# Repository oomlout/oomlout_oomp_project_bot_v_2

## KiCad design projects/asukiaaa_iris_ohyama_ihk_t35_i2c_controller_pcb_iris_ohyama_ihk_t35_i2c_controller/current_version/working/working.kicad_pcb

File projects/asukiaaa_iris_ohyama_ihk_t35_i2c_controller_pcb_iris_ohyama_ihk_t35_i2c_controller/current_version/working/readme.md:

# iris_ohyama_ihk_t35_i2c_controller_pcb
 
## summary 
* id: asukiaaa_iris_ohyama_ihk_t35_i2c_controller_pcb_iris_ohyama_ihk_t35_i2c_controller
* user: asukiaaa
* name: iris_ohyama_ihk_t35_i2c_controller_pcb
* board: iris_ohyama_ihk_t35_i2c_controller
* repo: https://github.com/asukiaaa/IRIS-OHYAMA-IHK-T35-I2C-Controller-PCB
* src_file_repo_kicad_pcb: main_pcb/IRIS-OHYAMA-IHK-T35-I2C-Controller.kicad_pcb
* src_file_repo_kicad_pcb_link: https://github.com/asukiaaa/IRIS-OHYAMA-IHK-T35-I2C-Controller-PCB/tree/master/main_pcb/IRIS-OHYAMA-IHK-T35-I2C-Controller.kicad_pcb

* src_file_repo_sch: main_pcb/IRIS-OHYAMA-IHK-T35-I2C-Controller.sch
* src_file_repo_sch_link: https://github.com/asukiaaa/IRIS-OHYAMA-IHK-T35-I2C-Controller-PCB/tree/master/main_pcb/IRIS-OHYAMA-IHK-T35-I2C-Controller.sch
* full details link: https://github.com/oomlout/oomlout_oomp_project_bot_v_2/tree/main/projects/asukiaaa_iris_ohyama_ihk_t35_i2c_controller_pcb_iris_ohyama_ihk_t35_i2c_controller/current_version/working  

## schematic  
  
[schematic (pdf)](working_schematic.pdf) 

## pcb  

[board (pdf)](working.pdf)  

## working_bom
| Id | Designator | Footprint | Quantity | Designation | Supplier and ref |  | None | 
| --- | --- | --- | --- | --- | --- | --- | --- | 
| 1 | J3 | JST_XH_S2B-XH-A_1x02_P2.50mm_Horizontal | 1 | thermistor |  |  | [''] | 
| 2 | C1,C2 | C_0402_1005Metric | 2 | 0.1uf |  |  | [''] | 
| 3 | CN1 | JST_XH_S5B-XH-A_1x05_P2.50mm_Horizontal | 1 | Conn_01x05 |  |  | [''] | 
| 4 | D1 | LED_0603_1608Metric | 1 | Level1 |  |  | [''] | 
| 5 | D2 | LED_0603_1608Metric | 1 | Level2 |  |  | [''] | 
| 6 | D3 | LED_0603_1608Metric | 1 | Level3 |  |  | [''] | 
| 7 | D4 | LED_0603_1608Metric | 1 | Level4 |  |  | [''] | 
| 8 | D5 | LED_0603_1608Metric | 1 | Level5 |  |  | [''] | 
| 9 | D6 | LED_0603_1608Metric | 1 | Level6 |  |  | [''] | 
| 10 | D7 | LED_0603_1608Metric | 1 | NomalState |  |  | [''] | 
| 11 | D8 | LED_0603_1608Metric | 1 | OilState |  |  | [''] | 
| 12 | D9,D10,D11,D12,D13,D14 | D_SOD-123F | 6 | D |  |  | [''] | 
| 13 | J1 | NS-Tech_Grove_1x04_P2mm_Horizontal | 1 | Grove |  |  | [''] | 
| 14 | KEY1 | SW_PUSH_6mm_center_like_smd | 1 | normal_power |  |  | [''] | 
| 15 | KEY2 | SW_PUSH_6mm_center_like_smd | 1 | power_up |  |  | [''] | 
| 16 | KEY3 | SW_PUSH_6mm_center_like_smd | 1 | power_down |  |  | [''] | 
| 17 | KEY5 | SW_PUSH_6mm_center_like_smd | 1 | oil_power |  |  | [''] | 
| 18 | Q1,Q2,Q3,Q4 | SOT-23 | 4 | Q_NMOS_DGS |  |  | [''] | 
| 19 | R1,R2,R3,R4,R5,R6,R7,R8,R12,R14,R15,R16,R17,R18,R19,R20 | R_0603_1608Metric | 16 | 1k |  |  | [''] | 
| 20 | R9,R10,R11,R13 | R_0603_1608Metric | 4 | 2k |  |  | [''] | 
| 21 | U1 | SOP-14_4.4x9.2mm_P1.27mm | 1 | 74HC164 |  |  | [''] | 
| 22 | U2 | QFN-32-1EP_5x5mm_P0.5mm_EP3.1x3.1mm | 1 | ATmega328P-MU |  |  | [''] | 
| 23 | J2 | 2x03_P2.54mm_Pads | 1 | Conn_01x06 |  |  | [''] | 

## bom_schematic
| Ref | Qnty | Value | Cmp name | Footprint | Description | Vendor | DNP | 
| --- | --- | --- | --- | --- | --- | --- | --- | 
| C1, C2 | 2 | 0.1uf | C | Capacitor_SMD:C_0402_1005Metric | Unpolarized capacitor |  |  | 
| CN1 | 1 | Conn_01x05 | Conn_01x05 | Connector_JST:JST_XH_S5B-XH-A_1x05_P2.50mm_Horizontal | Generic connector, single row, 01x05, script generated (kicad-library-utils/schlib/autogen/connector/) |  |  | 
| D1 | 1 | Level1 | LED | LED_SMD:LED_0603_1608Metric | Light emitting diode |  |  | 
| D2 | 1 | Level2 | LED | LED_SMD:LED_0603_1608Metric | Light emitting diode |  |  | 
| D3 | 1 | Level3 | LED | LED_SMD:LED_0603_1608Metric | Light emitting diode |  |  | 
| D4 | 1 | Level4 | LED | LED_SMD:LED_0603_1608Metric | Light emitting diode |  |  | 
| D5 | 1 | Level5 | LED | LED_SMD:LED_0603_1608Metric | Light emitting diode |  |  | 
| D6 | 1 | Level6 | LED | LED_SMD:LED_0603_1608Metric | Light emitting diode |  |  | 
| D7 | 1 | NomalState | LED | LED_SMD:LED_0603_1608Metric | Light emitting diode |  |  | 
| D8 | 1 | OilState | LED | LED_SMD:LED_0603_1608Metric | Light emitting diode |  |  | 
| D9, D10, D11, D12, D13, D14 | 6 | D | D | Diode_SMD:D_SOD-123F | Diode |  |  | 
| J1 | 1 | Grove | Conn_01x04 | my-kicad-footprints:NS-Tech_Grove_1x04_P2mm_Horizontal | Generic connector, single row, 01x04, script generated (kicad-library-utils/schlib/autogen/connector/) |  |  | 
| J2 | 1 | Conn_01x06 | Conn_01x06 | my-kicad-footprints:2x03_P2.54mm_Pads | Generic connector, single row, 01x06, script generated (kicad-library-utils/schlib/autogen/connector/) |  |  | 
| J3 | 1 | thermistor | Conn_01x02 | Connector_JST:JST_XH_S2B-XH-A_1x02_P2.50mm_Horizontal | Generic connector, single row, 01x02, script generated (kicad-library-utils/schlib/autogen/connector/) |  |  | 
| JP1 | 1 | ADDR0_NO | Jumper_NO_Small-Device | Jumper:SolderJumper-2_P1.3mm_Open_RoundedPad1.0x1.5mm |  |  |  | 
| JP2 | 1 | ADDR1_NO | Jumper_NO_Small-Device | Jumper:SolderJumper-2_P1.3mm_Open_RoundedPad1.0x1.5mm |  |  |  | 
| KEY1 | 1 | normal_power | SW_Push | footprints:SW_PUSH_6mm_center_like_smd | Push button switch, generic, two pins |  |  | 
| KEY2 | 1 | power_up | SW_Push | footprints:SW_PUSH_6mm_center_like_smd | Push button switch, generic, two pins |  |  | 
| KEY3 | 1 | power_down | SW_Push | footprints:SW_PUSH_6mm_center_like_smd | Push button switch, generic, two pins |  |  | 
| KEY5 | 1 | oil_power | SW_Push | footprints:SW_PUSH_6mm_center_like_smd | Push button switch, generic, two pins |  |  | 
| Q1, Q2, Q3, Q4 | 4 | Q_NMOS_GSD | Q_NMOS_GSD | Package_TO_SOT_SMD:SOT-23 | N-MOSFET transistor, gate/source/drain |  |  | 
| R1, R2, R3, R4, R5, R6, R7, R8, R12, R14, R15, R16, R17, R18, R19, R20 | 16 | 1k | R | Resistor_SMD:R_0603_1608Metric | Resistor |  |  | 
| R9, R10, R11, R13 | 4 | 2k | R | Resistor_SMD:R_0603_1608Metric | Resistor |  |  | 
| U1 | 1 | 74HC164 | 74HC164 | footprints:SOP-14_4.4x9.2mm_P1.27mm | 8-bit serial-in parallel-out shift register |  |  | 
| U2 | 1 | ATmega328P-MU | ATmega328PB-MU-MCU_Microchip_ATmega | Package_DFN_QFN:QFN-32-1EP_5x5mm_P0.5mm_EP3.1x3.1mm |  |  |  |

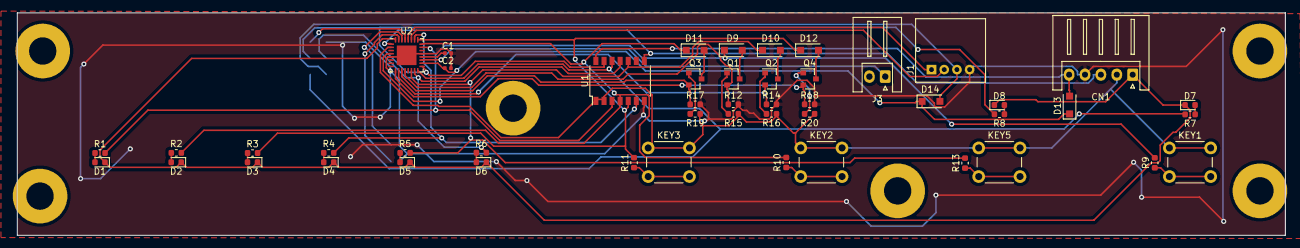
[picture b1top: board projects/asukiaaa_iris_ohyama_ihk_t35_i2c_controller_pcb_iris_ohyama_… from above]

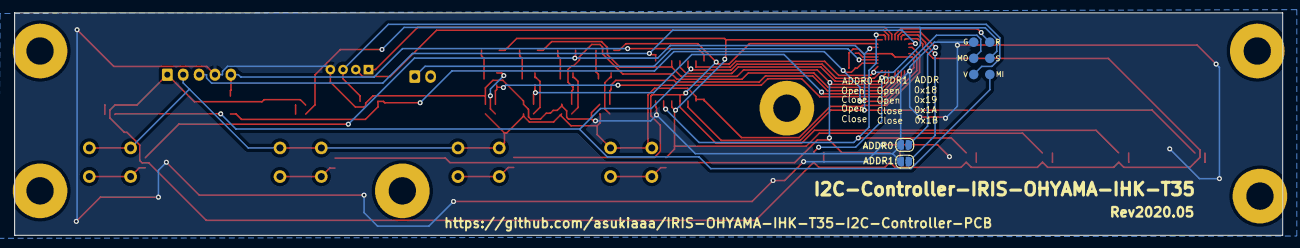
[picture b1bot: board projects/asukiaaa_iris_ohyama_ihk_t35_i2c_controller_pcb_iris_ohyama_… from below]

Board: 2 copper layers, 199.5 x 35.0 mm, 58 parts (3 on the bottom side), 46 nets.

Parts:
C1, C2: 0.1uf; C_0402_1005Metric
CN1: Conn_01x05; JST_XH_S5B-XH-A_1x05_P2.50mm_Horizontal
D1: Level1; LED_0603_1608Metric
D2: Level2; LED_0603_1608Metric
D3: Level3; LED_0603_1608Metric
D4: Level4; LED_0603_1608Metric
D5: Level5; LED_0603_1608Metric
D6: Level6; LED_0603_1608Metric
D7: NomalState; LED_0603_1608Metric
D8: OilState; LED_0603_1608Metric
D9, D10, D11, D12, D13, D14: D; D_SOD-123F
J1: Grove; NS-Tech_Grove_1x04_P2mm_Horizontal
J2: Conn_01x06; 2x03_P2.54mm_Pads
J3: thermistor; JST_XH_S2B-XH-A_1x02_P2.50mm_Horizontal
JP1: ADDR0_NO; SolderJumper-2_P1.3mm_Open_RoundedPad1.0x1.5mm
JP2: ADDR1_NO; SolderJumper-2_P1.3mm_Open_RoundedPad1.0x1.5mm
KEY1: normal_power; SW_PUSH_6mm_center_like_smd
KEY2: power_up; SW_PUSH_6mm_center_like_smd
KEY3: power_down; SW_PUSH_6mm_center_like_smd
KEY5: oil_power; SW_PUSH_6mm_center_like_smd
Q1, Q2, Q3, Q4: Q_NMOS_DGS; SOT-23
R1, R2, R3, R4, R5, R6, R7, R8, R12, R14, R15, R16, R17, R18, R19, R20: 1k; R_0603_1608Metric
R9, R10, R11, R13: 2k; R_0603_1608Metric
REF1, REF2, REF3, REF4, REF5, REF6: MountingHole_4.3mm_M4_Pad
U1: 74HC164; SOP-14_4.4x9.2mm_P1.27mm
U2: ATmega328P-MU; QFN-32-1EP_5x5mm_P0.5mm_EP3.1x3.1mm

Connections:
+5V: CN1.5, D13.2, U1.14
/A0: D9.1, R1.2, R9.2, U1.3, U2.23
/A1: D11.1, R2.2, R10.2, U1.4, U2.24
/A2: D12.1, R3.2, R11.2, U1.5, U2.25
/A3: R4.2, U1.6, U2.26
/A6: J3.1, U2.19
/ADDR0: JP1.1, U2.30
/ADDR1: JP2.1, U2.31
/CLK: CN1.3, U1.8, U2.1
/Controller_5V: C2.1, D13.1, D14.1, U2.4, U2.18
/D2: CN1.1, D1.1, D2.1, D3.1, D4.1, D5.1, D6.1, D7.1, D8.1, U2.32
/D4: CN1.2, KEY1.1, KEY2.1, KEY3.1, KEY5.1, R15.1, R16.1, R19.1, R20.1, U1.1, U1.2, U2.2
/D5: Q4.2, R18.1, U2.9
/D6: Q2.2, R14.1, U2.10
/D7: Q3.2, R17.1, U2.11
/D8: Q1.2, R12.1, U2.12
/D10: D10.1, R5.2, R13.2, U1.10, U2.14
/D11: J2.4, R6.2, U1.11, U2.15
/D12: J2.1, R7.2, U1.12, U2.16
/D13: J2.3, R8.2, U1.13, U2.17
/GROVE_5V: D14.2, J1.3, J2.2
/RST: J2.5, U2.29
/SCL: J1.1, U2.28
/SDA: J1.2, U2.27
GND: C1.2, C2.2, CN1.4, J1.4, J2.6, JP1.2, JP2.2, R12.2, R14.2, R17.2, R18.2, U1.7, U2.5, U2.21, U2.33
unnamed: C1.1, U2.20
unnamed: D1.2, R1.1
unnamed: D2.2, R2.1
unnamed: D3.2, R3.1
unnamed: D4.2, R4.1
unnamed: D5.2, R5.1
unnamed: D6.2, R6.1
unnamed: D7.2, R7.1
unnamed: D8.2, R8.1
unnamed: D9.2, Q1.3
unnamed: D10.2, Q2.3
unnamed: D11.2, Q3.3
unnamed: D12.2, Q4.3
unnamed: KEY1.2, R9.1
unnamed: KEY2.2, R10.1
unnamed: KEY3.2, R11.1
unnamed: KEY5.2, R13.1
unnamed: Q1.1, R15.2
unnamed: Q2.1, R16.2
unnamed: Q3.1, R19.2
unnamed: Q4.1, R20.2

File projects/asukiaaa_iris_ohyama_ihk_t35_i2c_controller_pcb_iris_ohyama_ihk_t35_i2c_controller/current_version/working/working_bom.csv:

"Id";"Designator";"Footprint";"Quantity";"Designation";"Supplier and ref";
1;"J3";"JST_XH_S2B-XH-A_1x02_P2.50mm_Horizontal";1;"thermistor";;;
2;"C1,C2";"C_0402_1005Metric";2;"0.1uf";;;
3;"CN1";"JST_XH_S5B-XH-A_1x05_P2.50mm_Horizontal";1;"Conn_01x05";;;
4;"D1";"LED_0603_1608Metric";1;"Level1";;;
5;"D2";"LED_0603_1608Metric";1;"Level2";;;
6;"D3";"LED_0603_1608Metric";1;"Level3";;;
7;"D4";"LED_0603_1608Metric";1;"Level4";;;
8;"D5";"LED_0603_1608Metric";1;"Level5";;;
9;"D6";"LED_0603_1608Metric";1;"Level6";;;
10;"D7";"LED_0603_1608Metric";1;"NomalState";;;
11;"D8";"LED_0603_1608Metric";1;"OilState";;;
12;"D9,D10,D11,D12,D13,D14";"D_SOD-123F";6;"D";;;
13;"J1";"NS-Tech_Grove_1x04_P2mm_Horizontal";1;"Grove";;;
14;"KEY1";"SW_PUSH_6mm_center_like_smd";1;"normal_power";;;
15;"KEY2";"SW_PUSH_6mm_center_like_smd";1;"power_up";;;
16;"KEY3";"SW_PUSH_6mm_center_like_smd";1;"power_down";;;
17;"KEY5";"SW_PUSH_6mm_center_like_smd";1;"oil_power";;;
18;"Q1,Q2,Q3,Q4";"SOT-23";4;"Q_NMOS_DGS";;;
19;"R1,R2,R3,R4,R5,R6,R7,R8,R12,R14,R15,R16,R17,R18,R19,R20";"R_0603_1608Metric";16;"1k";;;
20;"R9,R10,R11,R13";"R_0603_1608Metric";4;"2k";;;
21;"U1";"SOP-14_4.4x9.2mm_P1.27mm";1;"74HC164";;;
22;"U2";"QFN-32-1EP_5x5mm_P0.5mm_EP3.1x3.1mm";1;"ATmega328P-MU";;;
23;"J2";"2x03_P2.54mm_Pads";1;"Conn_01x06";;;

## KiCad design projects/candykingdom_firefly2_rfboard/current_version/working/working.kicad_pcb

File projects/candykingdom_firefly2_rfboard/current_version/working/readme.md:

# firefly2
 
## summary 
* id: candykingdom_firefly2_rfboard
* user: candykingdom
* name: firefly2
* board: rfboard
* repo: https://github.com/candykingdom/firefly2
* src_file_repo_kicad_pcb: hardware/rfboard/rfboard.kicad_pcb
* src_file_repo_kicad_pcb_link: https://github.com/candykingdom/firefly2/tree/master/hardware/rfboard/rfboard.kicad_pcb
* src_file_repo_kicad_sch: hardware/magnet-connector/magnet-connector.kicad_sch
* src_file_repo_kicad_sch_link: https://github.com/candykingdom/firefly2/tree/master/hardware/magnet-connector/magnet-connector.kicad_sch

* src_file_repo_sch: hardware/rfboard/rfboard.sch
* src_file_repo_sch_link: https://github.com/candykingdom/firefly2/tree/master/hardware/rfboard/rfboard.sch
* full details link: https://github.com/oomlout/oomlout_oomp_project_bot_v_2/tree/main/projects/candykingdom_firefly2_rfboard/current_version/working

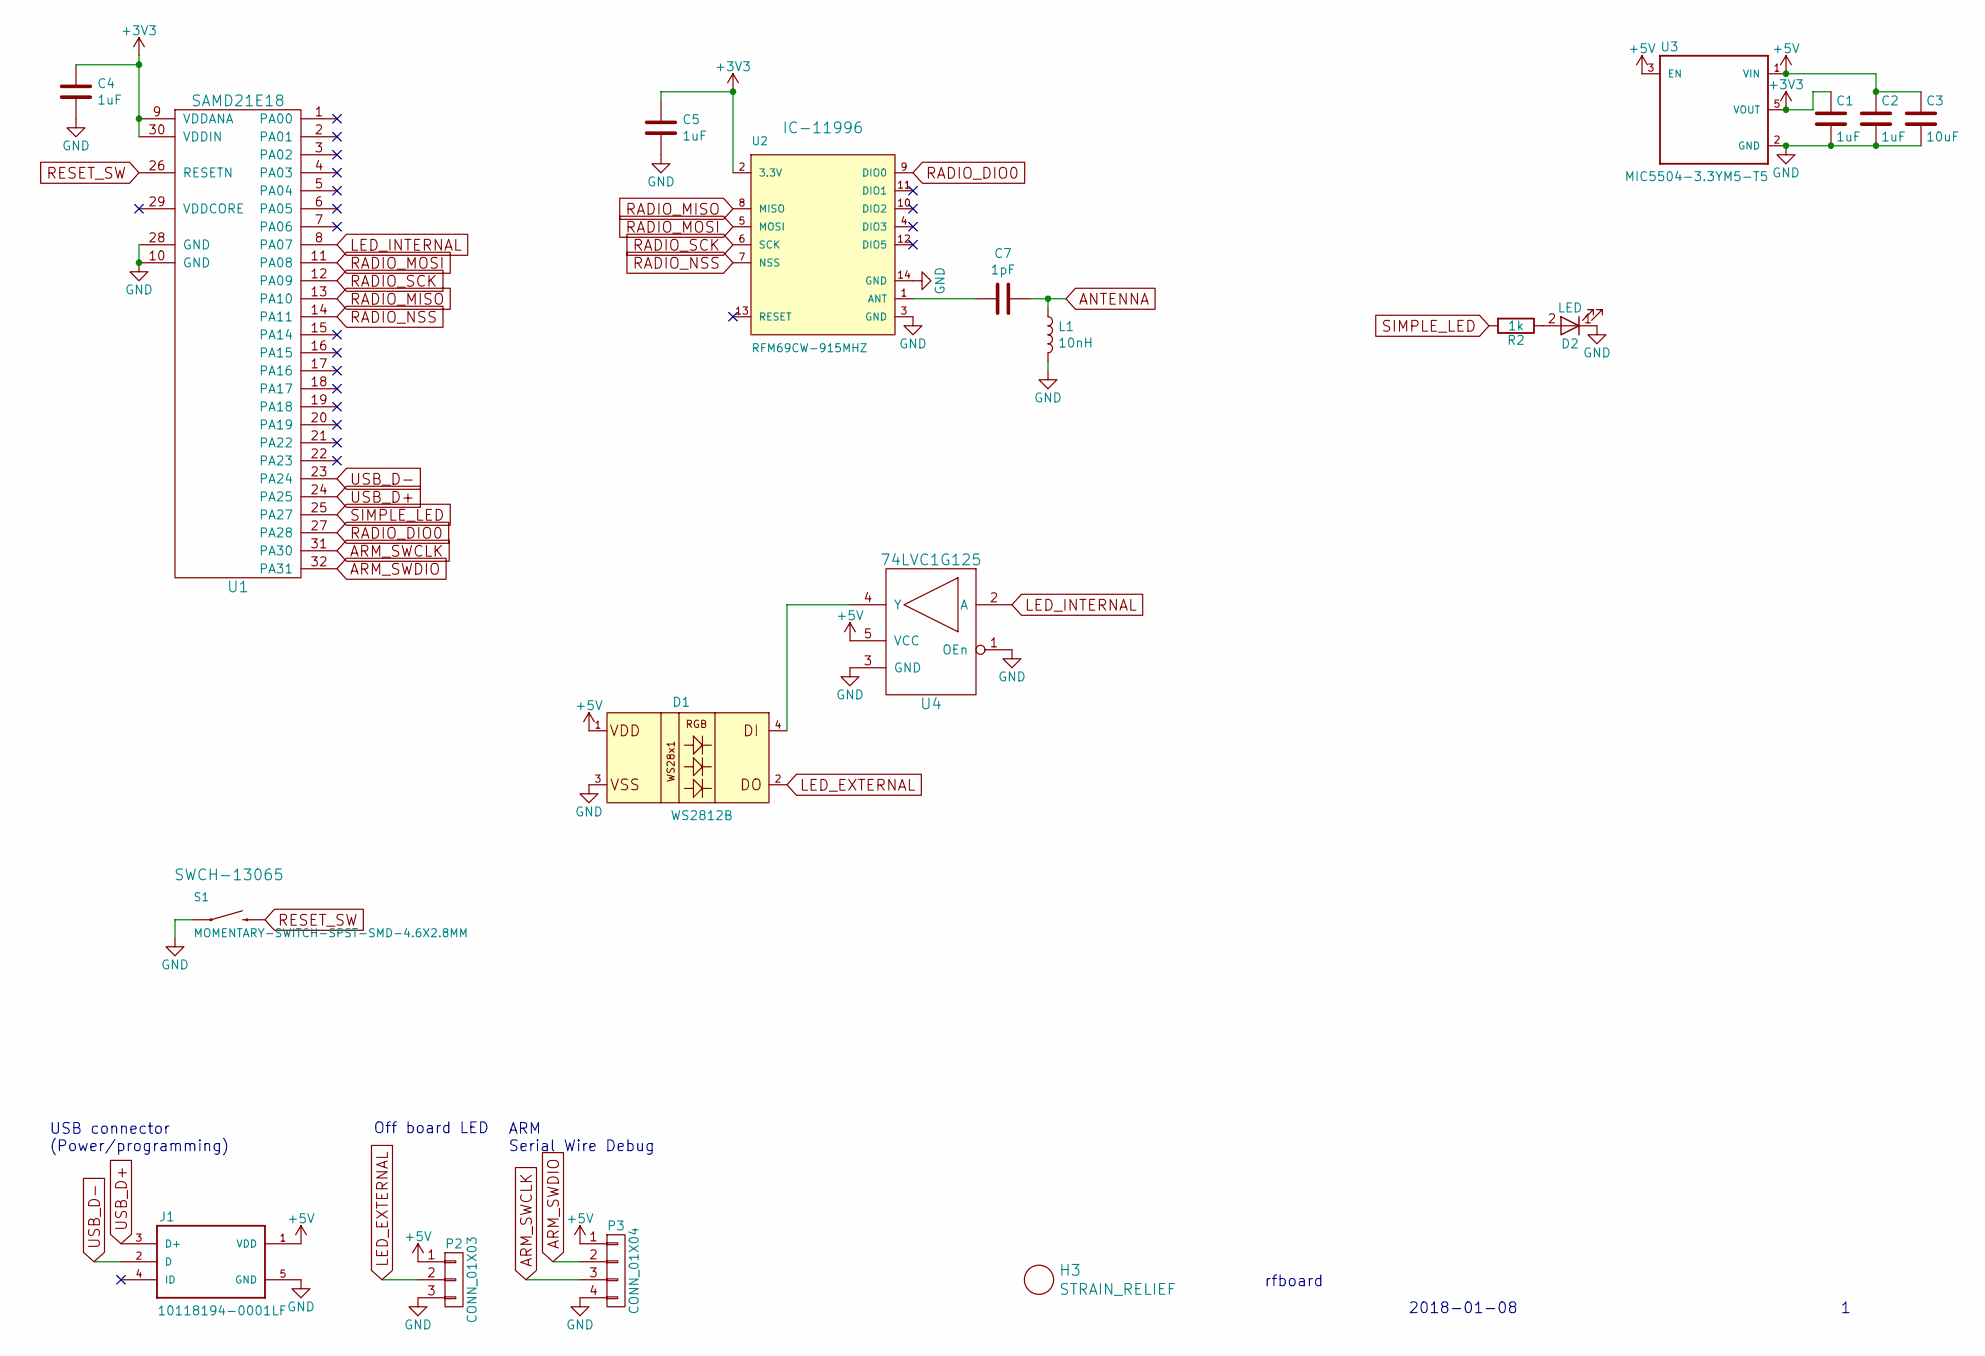
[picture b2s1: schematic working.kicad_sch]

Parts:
C1, C2, C4, C5: 1uF; C_0603_1608Metric
C3: 10uF; C_0805_2012Metric
C7: 1pF; C_0603_1608Metric
D1: WS2812B
D2: LED; LED_0603_1608Metric
H3: STRAIN_RELIEF; 3_pin_2.54mm_pitch_strain_relief
J1: 10118194-0001LF; FRAMATOME_10118194-0001LF_fixed_bridges
L1: 10nH; L_0603_1608Metric
P2: CONN_01X03; PinHeader_1x03_P2.54mm_Vertical
P3: CONN_01X04; PinHeader_1x04_P2.54mm_Vertical
R2: 1k; R_0603_1608Metric
S1: MOMENTARY-SWITCH-SPST-SMD-4.6X2.8MM; TACTILE_SWITCH_SMD_4.6X2.8MM
U1: SAMD21E18; TQFP32-08
U2: RFM69CW-915MHZ; RFM69CW-minimalpads
U3: MIC5504-3.3YM5-T5; SOT23-5P95_280X145XL45X37N
U4: 74LVC1G125; SOT-353_SC-70-5

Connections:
+3V3: C1.1, C4.1, C5.1, U1.9 (VDDANA), U1.30 (VDDIN), U2.2 (3.3V), U3.5 (VOUT)
+5V: C2.1, C3.1, D1.1 (VDD), J1.1 (VDD), P2.1, P3.1, U3.1 (VIN), U3.3 (EN), U4.5 (VCC)
ANTENNA: C7.1, L1.1
ARM_SWCLK: P3.3, U1.31 (PA30)
ARM_SWDIO: P3.2, U1.32 (PA31)
GND: C1.2, C2.2, C3.2, C4.2, C5.2, D1.3 (VSS), D2.1 (K), J1.5 (GND), L1.2, P2.3, P3.4, S1.1, S1.2 (1), U1.10 (GND), U1.28 (GND), U2.3 (GND), U2.14 (GND), U3.2 (GND), U4.1 (OEn), U4.3 (GND)
LED_EXTERNAL: D1.2 (DO), P2.2
LED_INTERNAL: U1.8 (PA07), U4.2 (A)
unnamed: C7.2, U2.1 (ANT)
unnamed: D1.4 (DI), U4.4 (Y)
unnamed: D2.2 (A), R2.1
RADIO_DIO0: U1.27 (PA28), U2.9 (DIO0)
RADIO_MISO: U1.13 (PA10), U2.8 (MISO)
RADIO_MOSI: U1.11 (PA08), U2.5 (MOSI)
RADIO_NSS: U1.14 (PA11), U2.7 (NSS)
RADIO_SCK: U1.12 (PA09), U2.6 (SCK)
RESET_SW: S1.3 (2), S1.4 (2), U1.26 (RESETN)
SIMPLE_LED: R2.2, U1.25 (PA27)
USB_D+: J1.3 (D+), U1.24 (PA25)
USB_D-: J1.2 (D), U1.23 (PA24)

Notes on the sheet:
Off board LED
rfboard
2018-01-08
USB connector (Power/programming)
ARM Serial Wire Debug

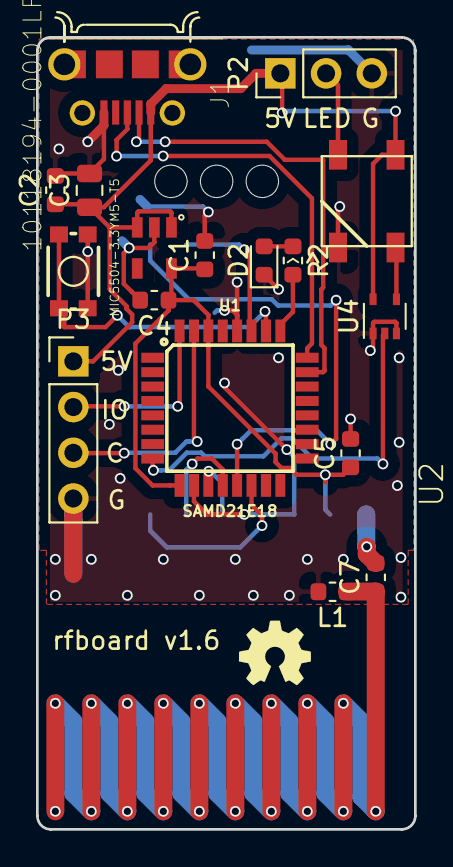
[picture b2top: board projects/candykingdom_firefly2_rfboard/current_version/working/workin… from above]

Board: 2 copper layers, 21.0 x 44.0 mm, 19 parts (1 on the bottom side), 20 nets.

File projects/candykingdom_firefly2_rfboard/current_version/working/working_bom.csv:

"Id";"Designator";"Footprint";"Quantity";"Designation";"Supplier and ref";
1;"C3";"C_0805_2012Metric";1;"10uF";;;
2;"U4";"SOT-353_SC-70-5";1;"74LVC1G125";;;
3;"C1,C2,C4,C5";"C_0603_1608Metric";4;"1uF";;;
4;"C7";"C_0603_1608Metric";1;"1pF";;;
5;"D1";"WS2812B";1;"WS2812B";;;
6;"H3";"3_pin_2.54mm_pitch_strain_relief";1;"STRAIN_RELIEF";;;
7;"J1";"FRAMATOME_10118194-0001LF_fixed_bridges";1;"10118194-0001LF";;;
8;"L1";"L_0603_1608Metric";1;"10nH";;;
9;"R2";"R_0603_1608Metric";1;"1k";;;
10;"U1";"TQFP32-08";1;"SAMD21E18";;;
11;"U3";"SOT23-5P95_280X145XL45X37N";1;"MIC5504-3.3YM5-T5";;;
12;"S1";"TACTILE_SWITCH_SMD_4.6X2.8MM";1;"MOMENTARY-SWITCH-SPST-SMD-4.6X2.8MM";;;
13;"P3";"PinHeader_1x04_P2.54mm_Vertical";1;"CONN_01X04";;;
14;"D2";"LED_0603_1608Metric";1;"LED";;;
15;"P2";"PinHeader_1x03_P2.54mm_Vertical";1;"CONN_01X03";;;
16;"G***";"OSHW_LOGO_4mm";1;"OSHW_LOGO_4mm";;;
17;"U2";"RFM69CW-minimalpads";1;"RFM69CW-915MHZ";;;

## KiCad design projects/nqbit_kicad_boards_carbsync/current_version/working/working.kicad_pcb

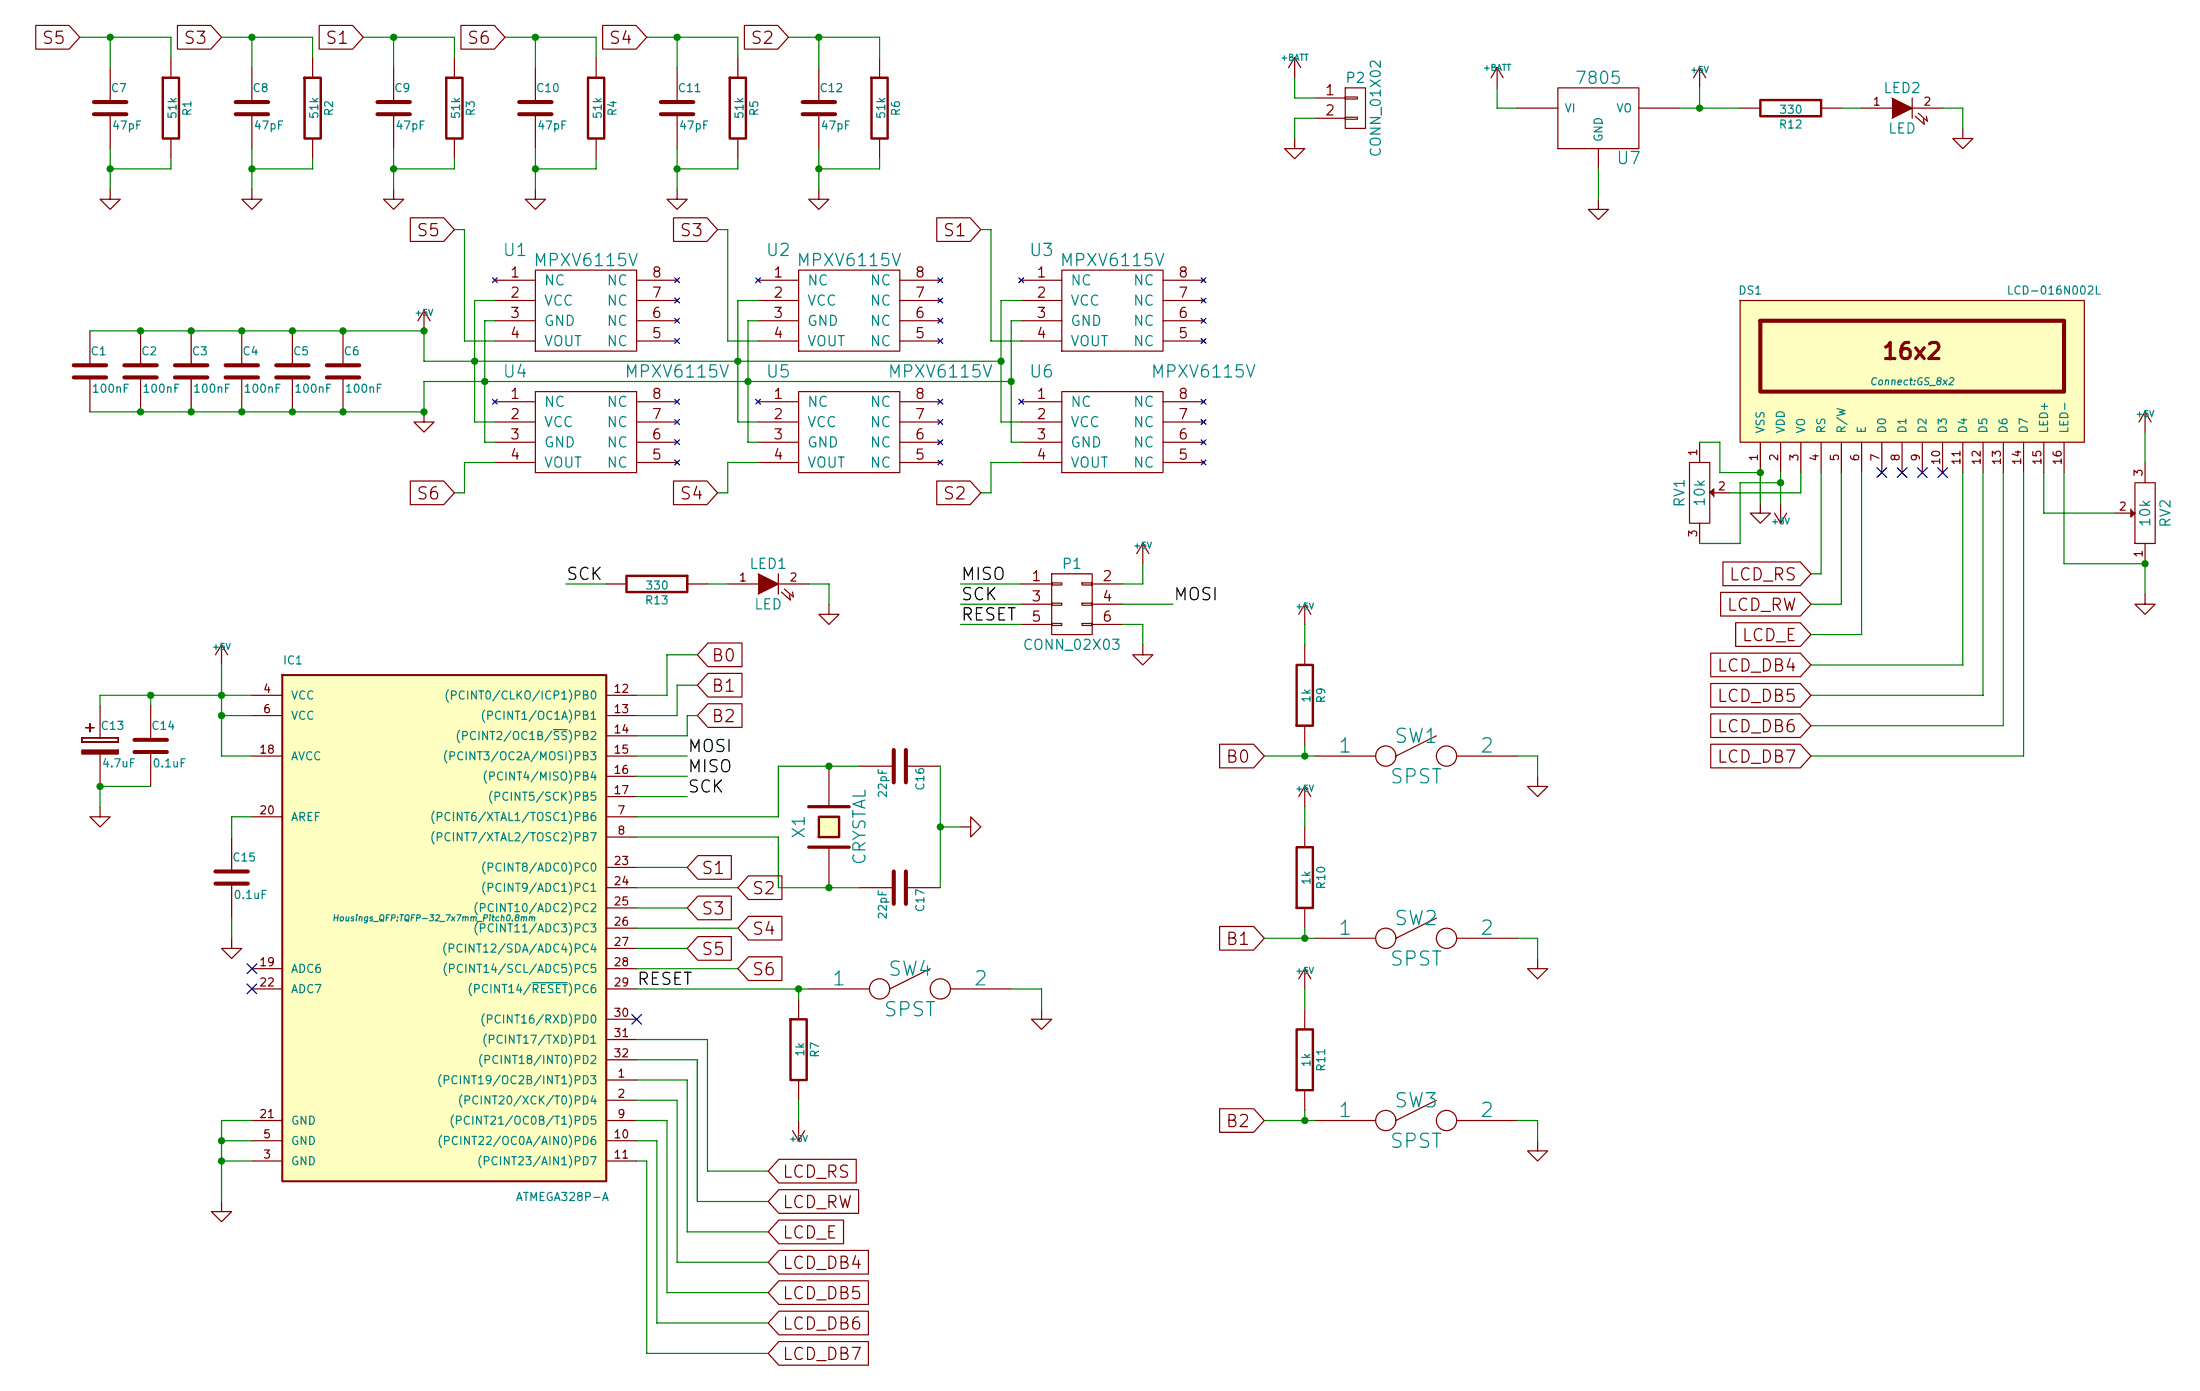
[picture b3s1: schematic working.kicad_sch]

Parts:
C1, C2, C3, C4, C5, C6: 100nF; C_0805
C7, C8, C9, C10, C11, C12: 47pF; C_0805
C13: 4.7uF; Elko_vert_11x5mm_RM2.5
C14, C15: 0.1uF; C_0805
C16, C17: 22pF; C_0805
DS1: LCD-016N002L; GS_8x2
IC1: ATMEGA328P-A; TQFP-32_7x7mm_Pitch0.8mm
LED1, LED2: LED; LED-0805
P1: CONN_02X03; Pin_Header_Straight_2x03
P2: CONN_01X02; Pin_Header_Straight_1x02
R1, R2, R3, R4, R5, R6: 51k; R_0805
R7, R9, R10, R11: 1k; R_0805
R12, R13: 330; R_0805
RV1, RV2: 10k; Potentiometer_VishaySpectrol-Econtrim-Type36M
SW1, SW2, SW3, SW4: SPST; SW_PUSH_SMALL
U1, U2, U3, U4, U5, U6: MPXV6115V
U7: 7805; LM78XXV
X1: CRYSTAL; HC-49USX_SMD

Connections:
+5V: C1.1, C2.1, C3.1, C4.1, C5.1, C6.1, C13.1, C14.1, DS1.2 (VDD), IC1.4 (VCC), IC1.6 (VCC), IC1.18 (AVCC), P1.2, R7.2, R9.2, R10.2, R11.2, R12.2, RV1.3, RV2.3, U1.2 (VCC), U2.2 (VCC), U3.2 (VCC), U4.2 (VCC), U5.2 (VCC), U6.2 (VCC), U7.VO
+BATT: P2.1, U7.VI
/MISO: IC1.16 ((PCINT4/MISO)PB4), P1.1
/MOSI: IC1.15 ((PCINT3/OC2A/MOSI)PB3), P1.4
/RESET: IC1.29 ((PCINT14/~RESET)PC6), P1.5, R7.1, SW4.1
/SCK: IC1.17 ((PCINT5/SCK)PB5), P1.3, R13.2
B0: IC1.12 ((PCINT0/CLKO/ICP1)PB0), R9.1, SW1.1
B1: IC1.13 ((PCINT1/OC1A)PB1), R10.1, SW2.1
B2: IC1.14 ((PCINT2/OC1B/~SS)PB2), R11.1, SW3.1
GND: C1.2, C2.2, C3.2, C4.2, C5.2, C6.2, C7.2, C8.2, C9.2, C10.2, C11.2, C12.2, C13.2, C14.2, C15.2, C16.1, C17.1, DS1.1 (VSS), DS1.16 (LED-), IC1.3 (GND), IC1.5 (GND), IC1.21 (GND), LED1.2 (K), LED2.2 (K), P1.6, P2.2, R1.2, R2.2, R3.2, R4.2, R5.2, R6.2, RV1.1, RV2.1, SW1.2, SW2.2, SW3.2, SW4.2, U1.3 (GND), U2.3 (GND), U3.3 (GND), U4.3 (GND), U5.3 (GND), U6.3 (GND), U7.GND
LCD_DB4: DS1.11 (D4), IC1.2 ((PCINT20/XCK/T0)PD4)
LCD_DB5: DS1.12 (D5), IC1.9 ((PCINT21/OC0B/T1)PD5)
LCD_DB6: DS1.13 (D6), IC1.10 ((PCINT22/OC0A/AIN0)PD6)
LCD_DB7: DS1.14 (D7), IC1.11 ((PCINT23/AIN1)PD7)
LCD_E: DS1.6 (E), IC1.1 ((PCINT19/OC2B/INT1)PD3)
LCD_RS: DS1.4 (RS), IC1.31 ((PCINT17/TXD)PD1)
LCD_RW: DS1.5 (R/W), IC1.32 ((PCINT18/INT0)PD2)
unnamed: C15.1, IC1.20 (AREF)
unnamed: C16.2, IC1.7 ((PCINT6/XTAL1/TOSC1)PB6), X1.2
unnamed: C17.2, IC1.8 ((PCINT7/XTAL2/TOSC2)PB7), X1.1
unnamed: DS1.3 (VO), RV1.2
unnamed: DS1.15 (LED+), RV2.2
unnamed: LED1.1 (A), R13.1
unnamed: LED2.1 (A), R12.1
S1: C9.1, IC1.23 ((PCINT8/ADC0)PC0), R3.1, U3.4 (VOUT)
S2: C12.1, IC1.24 ((PCINT9/ADC1)PC1), R6.1, U6.4 (VOUT)
S3: C8.1, IC1.25 ((PCINT10/ADC2)PC2), R2.1, U2.4 (VOUT)
S4: C11.1, IC1.26 ((PCINT11/ADC3)PC3), R5.1, U5.4 (VOUT)
S5: C7.1, IC1.27 ((PCINT12/SDA/ADC4)PC4), R1.1, U1.4 (VOUT)
S6: C10.1, IC1.28 ((PCINT14/SCL/ADC5)PC5), R4.1, U4.4 (VOUT)

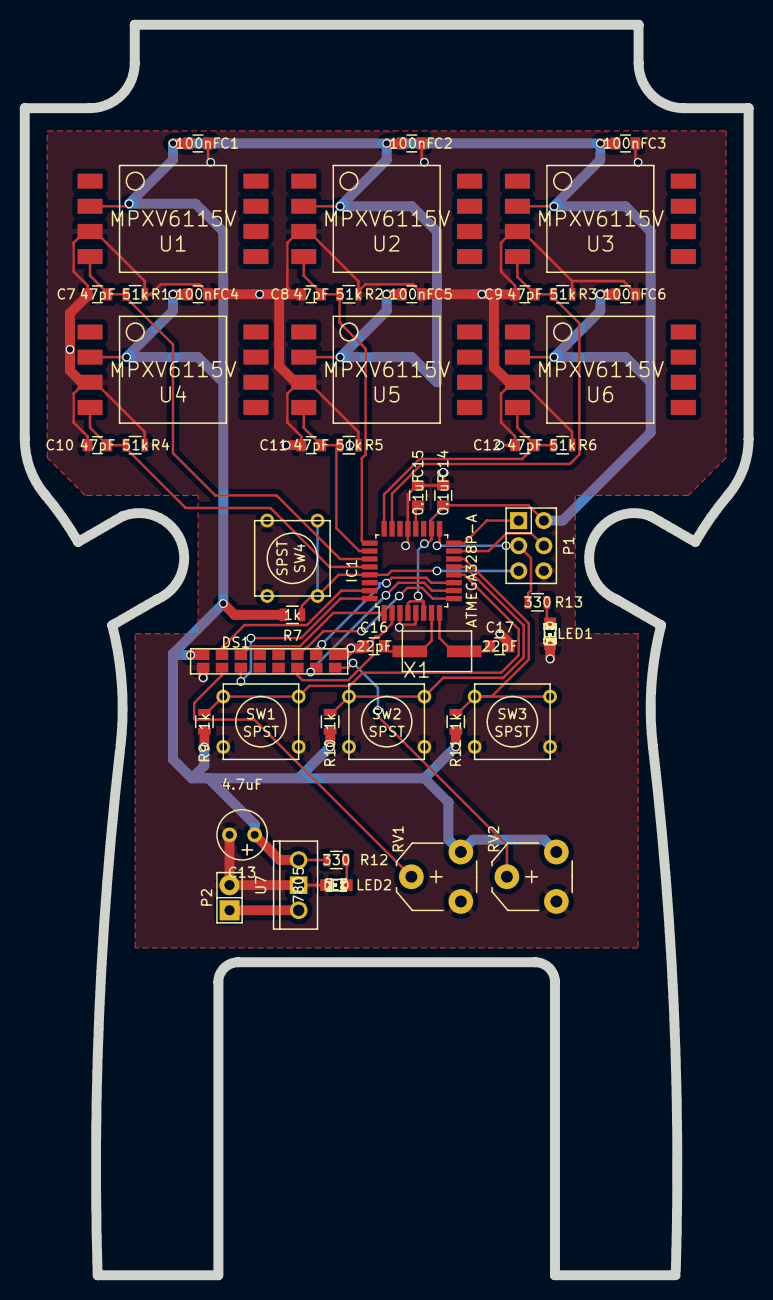
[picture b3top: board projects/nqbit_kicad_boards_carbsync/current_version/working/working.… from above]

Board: 2 copper layers, 73.1 x 126.3 mm, 49 parts (0 on the bottom side), 30 nets.

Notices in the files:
projects/alexisvl_os2_gfx/current_version/working/working.kicad_pcb:
© 2020 ALEXIS LOCKWOOD. CC BY-NC-SA 3.0
projects/esden_bitmagic_bm1/current_version/working/working.kicad_sch:
(C) 2017 Piotr Esden-Tempski
(C) 2017 1BitSquared
License: CC-BY-SA V4.0
